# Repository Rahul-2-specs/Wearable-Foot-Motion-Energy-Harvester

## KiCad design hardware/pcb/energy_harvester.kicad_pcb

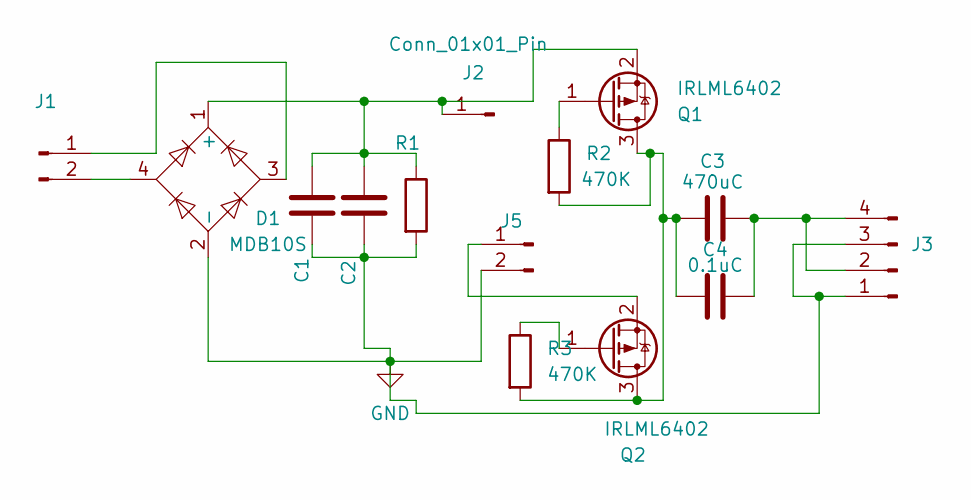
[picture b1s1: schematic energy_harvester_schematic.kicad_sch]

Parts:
C1: 10uC; C_Disc_D5.0mm_W2.5mm_P5.00mm
C2: 2200uC; C_Radial_D10.0mm_H20.0mm_P5.00mm
C3: 470uC; C_Radial_D8.0mm_H11.5mm_P3.50mm
C4: 0.1uC; C_Disc_D5.0mm_W2.5mm_P5.00mm
D1: MDB10S; DIP-4_W7.62mm_LongPads
J1, J5: Conn_01x02_Pin; PinHeader_1x02_P2.54mm_Vertical
J2: Conn_01x01_Pin; PinHeader_1x01_P2.54mm_Vertical
J3: Conn_01x04_Pin; JST_EH_B4B-EH-A_1x04_P2.50mm_Vertical
Q1, Q2: IRLML6402; SOT-23
R1: 1Meg; R_1206_3216Metric
R2, R3: 470K; R_1206_3216Metric

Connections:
GND: C1.2, C2.2, D1.2 (-), J3.1, J3.3, J5.2, R1.2
unnamed: C1.1, C2.1, D1.1 (+), J2.1, Q1.2 (S), R1.1
unnamed: D1.3, J1.1
unnamed: D1.4, J1.2
unnamed: C3.2, C4.2, J3.2, J3.4
unnamed: J5.1, Q2.2 (S)
unnamed: C3.1, C4.1, Q1.3 (D), Q2.3 (D), R2.2, R3.2
unnamed: Q1.1 (G), R2.1
unnamed: Q2.1 (G), R3.1

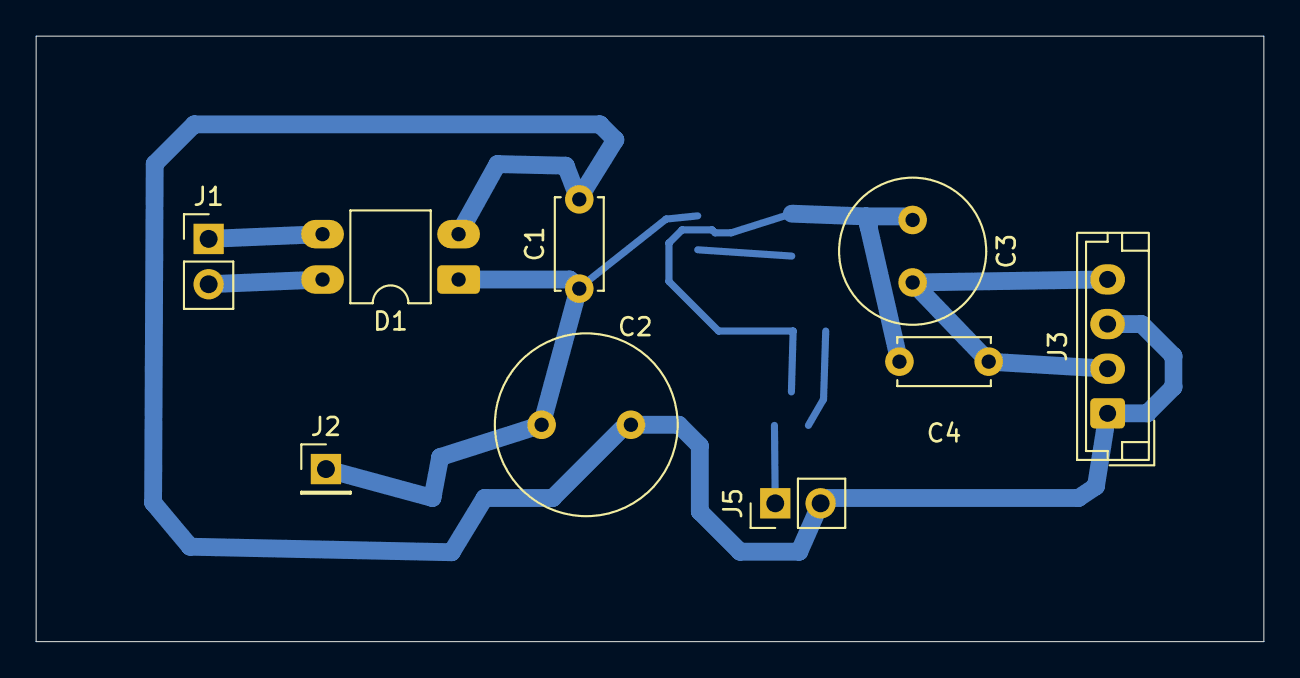
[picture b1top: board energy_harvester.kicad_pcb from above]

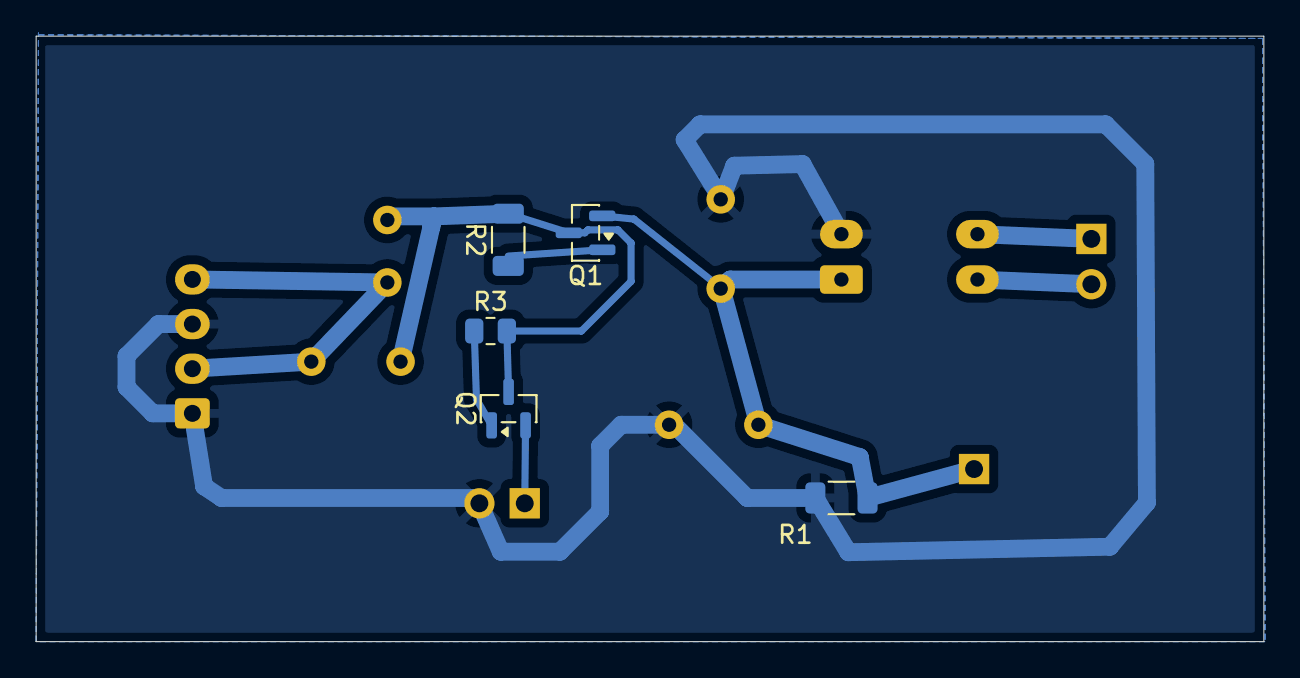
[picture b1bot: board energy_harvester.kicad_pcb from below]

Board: 2 copper layers, 68.8 x 33.9 mm, 14 parts (5 on the bottom side), 9 nets.
